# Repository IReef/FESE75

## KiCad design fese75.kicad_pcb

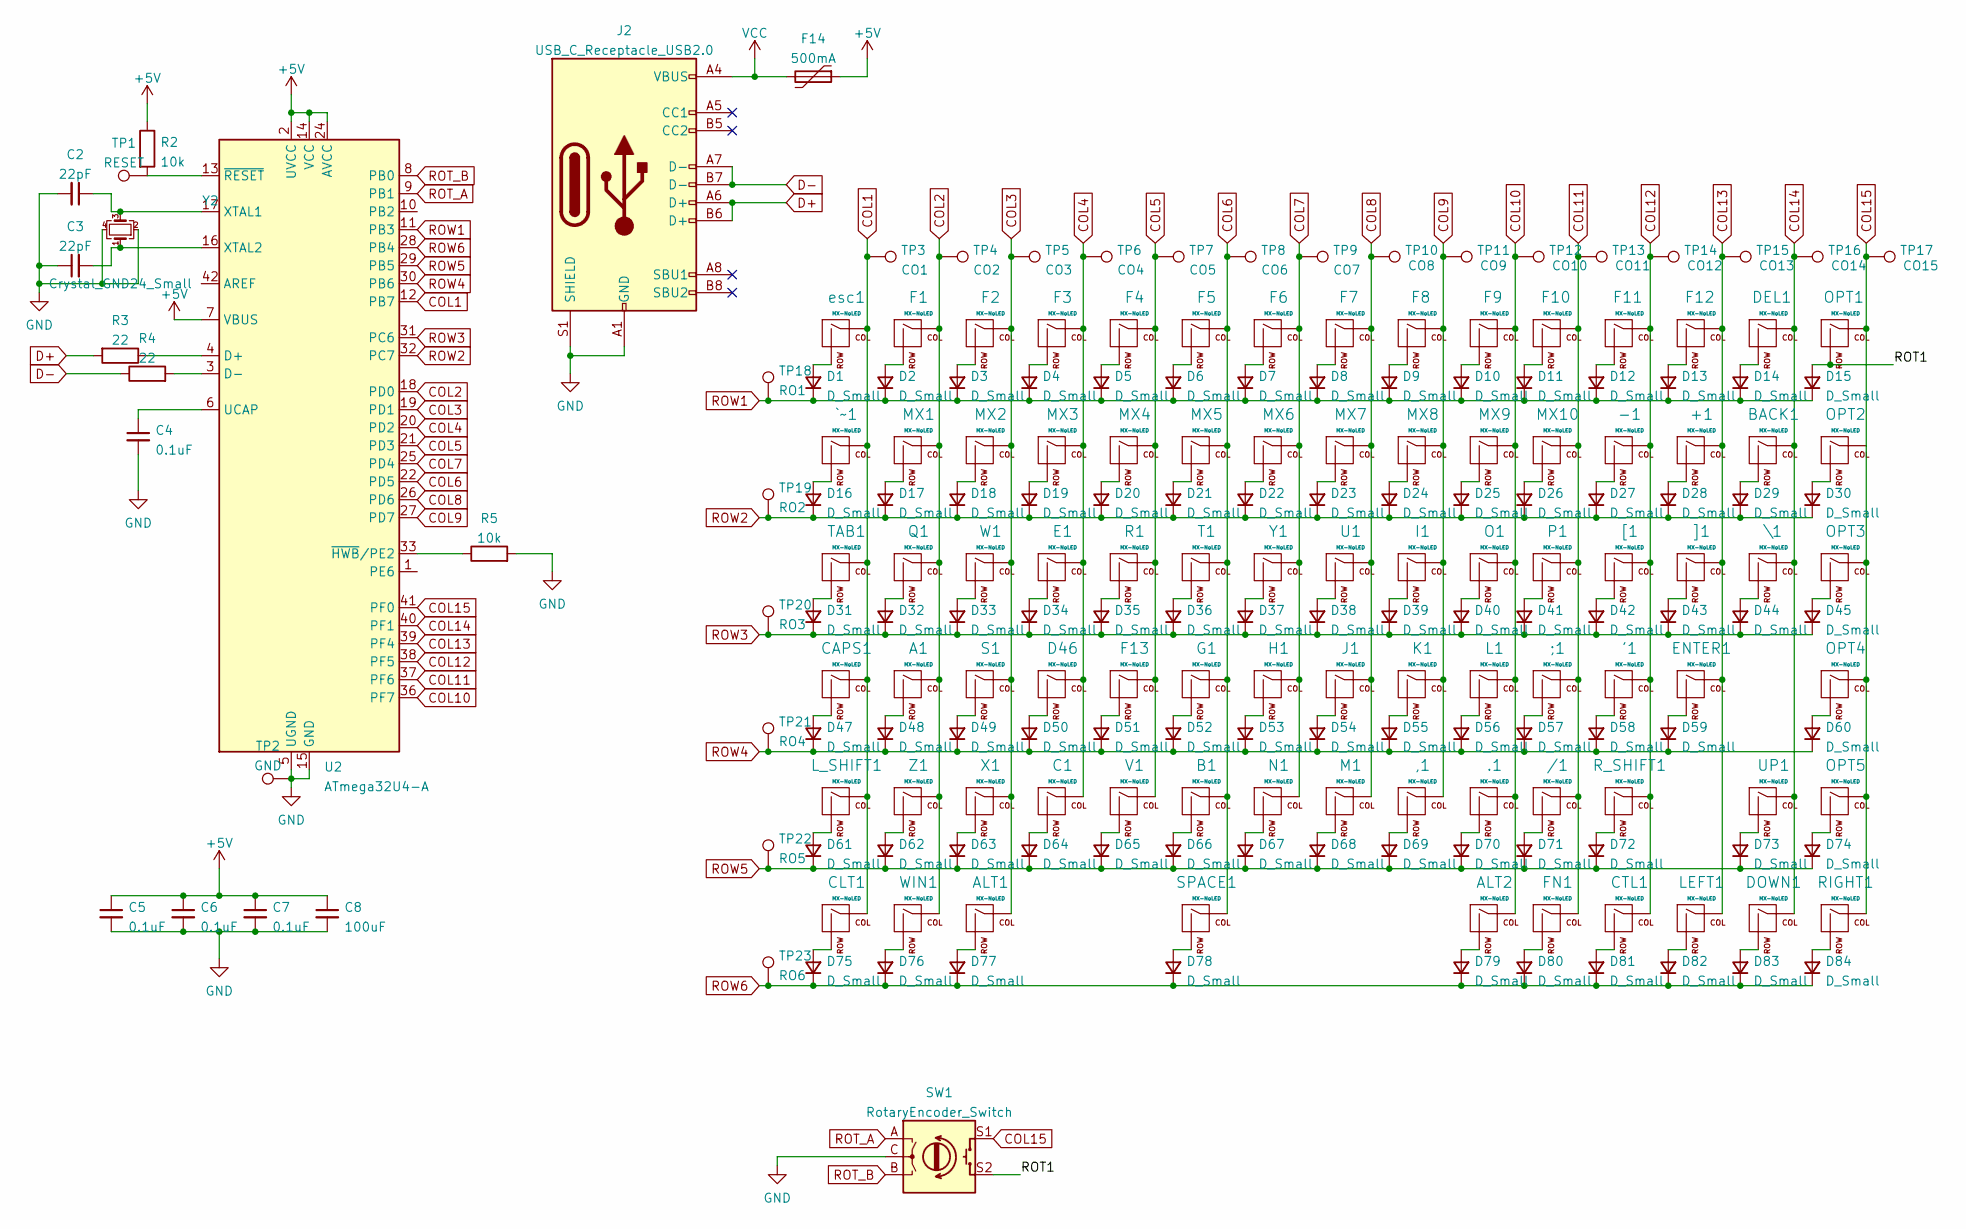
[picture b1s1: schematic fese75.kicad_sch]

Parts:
'1: MX-NoLED; SW_Hotswap_Kailh_1.00u
+1: MX-NoLED; SW_Hotswap_Kailh_1.00u
,1: MX-NoLED; SW_Hotswap_Kailh_1.00u
-1: MX-NoLED; SW_Hotswap_Kailh_1.00u
.1: MX-NoLED; SW_Hotswap_Kailh_1.00u
/1: MX-NoLED; SW_Hotswap_Kailh_1.00u
;1: MX-NoLED; SW_Hotswap_Kailh_1.00u
A1: MX-NoLED; SW_Hotswap_Kailh_1.00u
ALT1: MX-NoLED; SW_Hotswap_Kailh_1.25u
ALT2: MX-NoLED; SW_Hotswap_Kailh_1.00u
B1: MX-NoLED; SW_Hotswap_Kailh_1.00u
BACK1: MX-NoLED; SW_Hotswap_Kailh_2.00u
C1: MX-NoLED; SW_Hotswap_Kailh_1.00u
C2, C3: 22pF; C_0603_1608Metric
C4, C5, C6, C7: 0.1uF; C_0603_1608Metric
C8: 100uF; C_0603_1608Metric
CAPS1: MX-NoLED; SW_Hotswap_Kailh_1.75u
CLT1: MX-NoLED; SW_Hotswap_Kailh_1.25u
CTL1: MX-NoLED; SW_Hotswap_Kailh_1.00u
D1, D2, D3, D4, D5, D6, D7, D8, D9, D10, D11, D12, D13, D14, D15, D16, D17, D18, D19, D20, D21, D22, D23, D24, D25, D26, D27, D28, D29, D30, D31, D32, D33, D34, D35, D36, D37, D38, D39, D40, D41, D42, D43, D44, D45, D47, D48, D49, D50, D51, D52, D53, D54, D55, D56, D57, D58, D59, D60, D61, D62, D63, D64, D65, D66, D67, D68, D69, D70, D71, D72, D73, D74, D75, D76, D77, D78, D79, D80, D81, D82, D83, D84: D_Small; D_SOD-123
D46: MX-NoLED; SW_Hotswap_Kailh_1.00u
DEL1: MX-NoLED; SW_Hotswap_Kailh_1.00u
DOWN1: MX-NoLED; SW_Hotswap_Kailh_1.00u
E1: MX-NoLED; SW_Hotswap_Kailh_1.00u
ENTER1: MX-NoLED; SW_Hotswap_Kailh_2.25u
F1, F2, F3, F4, F5, F6, F7, F8, F9, F10, F11, F12, F13: MX-NoLED; SW_Hotswap_Kailh_1.00u
F14: 500mA; Fuse_1206_3216Metric
FN1: MX-NoLED; SW_Hotswap_Kailh_1.00u
G1: MX-NoLED; SW_Hotswap_Kailh_1.00u
H1: MX-NoLED; SW_Hotswap_Kailh_1.00u
I1: MX-NoLED; SW_Hotswap_Kailh_1.00u
J1: MX-NoLED; SW_Hotswap_Kailh_1.00u
J2: USB_C_Receptacle_USB2.0; USB_C_Receptacle_GCT_USB4085
K1: MX-NoLED; SW_Hotswap_Kailh_1.00u
L1: MX-NoLED; SW_Hotswap_Kailh_1.00u
LEFT1: MX-NoLED; SW_Hotswap_Kailh_1.00u
L_SHIFT1: MX-NoLED; SW_Hotswap_Kailh_2.25u
M1: MX-NoLED; SW_Hotswap_Kailh_1.00u
MX1, MX2, MX3, MX4, MX5, MX6, MX7, MX8, MX9, MX10: MX-NoLED; SW_Hotswap_Kailh_1.00u
N1: MX-NoLED; SW_Hotswap_Kailh_1.00u
O1: MX-NoLED; SW_Hotswap_Kailh_1.00u
OPT1, OPT2, OPT3, OPT4, OPT5: MX-NoLED; SW_Hotswap_Kailh_1.00u
P1: MX-NoLED; SW_Hotswap_Kailh_1.00u
Q1: MX-NoLED; SW_Hotswap_Kailh_1.00u
R1: MX-NoLED; SW_Hotswap_Kailh_1.00u
R2, R5: 10k; R_0603_1608Metric
R3, R4: 22; R_0603_1608Metric
RIGHT1: MX-NoLED; SW_Hotswap_Kailh_1.00u
R_SHIFT1: MX-NoLED; SW_Hotswap_Kailh_1.75u
S1: MX-NoLED; SW_Hotswap_Kailh_1.00u
SPACE1: MX-NoLED; SW_Hotswap_Kailh_6.25u
SW1: RotaryEncoder_Switch; RotaryEncoder_Alps_EC11E-Switch_Vertical_H20mm
T1: MX-NoLED; SW_Hotswap_Kailh_1.00u
TAB1: MX-NoLED; SW_Hotswap_Kailh_1.50u
TP1: RESET; TestPoint_THTPad_D1.0mm_Drill0.5mm
TP2: GND; TestPoint_THTPad_1.0x1.0mm_Drill0.5mm
TP3: CO1; TestPoint_THTPad_2.0x2.0mm_Drill1.0mm
TP4: CO2; TestPoint_THTPad_D2.0mm_Drill1.0mm
TP5: CO3; TestPoint_THTPad_D2.0mm_Drill1.0mm
TP6: CO4; TestPoint_THTPad_D2.0mm_Drill1.0mm
TP7: CO5; TestPoint_THTPad_D2.0mm_Drill1.0mm
TP8: CO6; TestPoint_THTPad_D2.0mm_Drill1.0mm
TP9: CO7; TestPoint_THTPad_D2.0mm_Drill1.0mm
TP10: CO8; TestPoint_THTPad_D2.0mm_Drill1.0mm
TP11: CO9; TestPoint_THTPad_D2.0mm_Drill1.0mm
TP12: CO10; TestPoint_THTPad_D2.0mm_Drill1.0mm
TP13: CO11; TestPoint_THTPad_D2.0mm_Drill1.0mm
TP14: CO12; TestPoint_THTPad_D2.0mm_Drill1.0mm
TP15: CO13; TestPoint_THTPad_D2.0mm_Drill1.0mm
TP16: CO14; TestPoint_THTPad_D2.0mm_Drill1.0mm
TP17: CO15; TestPoint_THTPad_D2.0mm_Drill1.0mm
TP18: RO1; TestPoint_THTPad_2.0x2.0mm_Drill1.0mm
TP19: RO2; TestPoint_THTPad_D2.0mm_Drill1.0mm
TP20: RO3; TestPoint_THTPad_D2.0mm_Drill1.0mm
TP21: RO4; TestPoint_THTPad_D2.0mm_Drill1.0mm
TP22: RO5; TestPoint_THTPad_D2.0mm_Drill1.0mm
TP23: RO6; TestPoint_THTPad_D2.0mm_Drill1.0mm
U1: MX-NoLED; SW_Hotswap_Kailh_1.00u
U2: ATmega32U4-A; TQFP-44_10x10mm_P0.8mm
UP1: MX-NoLED; SW_Hotswap_Kailh_1.00u
V1: MX-NoLED; SW_Hotswap_Kailh_1.00u
W1: MX-NoLED; SW_Hotswap_Kailh_1.00u
WIN1: MX-NoLED; SW_Hotswap_Kailh_1.25u
X1: MX-NoLED; SW_Hotswap_Kailh_1.00u
Y1: MX-NoLED; SW_Hotswap_Kailh_1.00u
Y2: Crystal_GND24_Small; Crystal_SMD_3225-4Pin_3.2x2.5mm
Z1: MX-NoLED; SW_Hotswap_Kailh_1.00u
[1: MX-NoLED; SW_Hotswap_Kailh_1.00u
\1: MX-NoLED; SW_Hotswap_Kailh_1.50u
]1: MX-NoLED; SW_Hotswap_Kailh_1.00u
`~1: MX-NoLED; SW_Hotswap_Kailh_1.00u
esc1: MX-NoLED; SW_Hotswap_Kailh_1.00u

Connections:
+5V: C5.1, C6.1, C7.1, C8.1, F14.1, R2.1, U2.2 (UVCC), U2.7 (VBUS), U2.14 (VCC), U2.24 (AVCC), U2.34 (VCC), U2.44 (AVCC)
/ROT1: D15.2 (A), OPT1.2 (ROW), SW1.S2
COL1: CAPS1.1 (COL), CLT1.1 (COL), L_SHIFT1.1 (COL), TAB1.1 (COL), TP3.1, U2.12 (PB7), `~1.1 (COL), esc1.1 (COL)
COL2: A1.1 (COL), F1.1 (COL), MX1.1 (COL), Q1.1 (COL), TP4.1, U2.18 (PD0), WIN1.1 (COL), Z1.1 (COL)
COL3: ALT1.1 (COL), F2.1 (COL), MX2.1 (COL), S1.1 (COL), TP5.1, U2.19 (PD1), W1.1 (COL), X1.1 (COL)
COL4: C1.1 (COL), D46.1 (COL), E1.1 (COL), F3.1 (COL), MX3.1 (COL), TP6.1, U2.20 (PD2)
COL5: F4.1 (COL), F13.1 (COL), MX4.1 (COL), R1.1 (COL), TP7.1, U2.21 (PD3), V1.1 (COL)
COL6: B1.1 (COL), F5.1 (COL), G1.1 (COL), MX5.1 (COL), SPACE1.1 (COL), T1.1 (COL), TP8.1, U2.22 (PD5)
COL7: F6.1 (COL), H1.1 (COL), MX6.1 (COL), N1.1 (COL), TP9.1, U2.25 (PD4), Y1.1 (COL)
COL8: F7.1 (COL), J1.1 (COL), M1.1 (COL), MX7.1 (COL), TP10.1, U1.1 (COL), U2.26 (PD6)
COL9: ,1.1 (COL), F8.1 (COL), I1.1 (COL), K1.1 (COL), MX8.1 (COL), TP11.1, U2.27 (PD7)
COL10: .1.1 (COL), ALT2.1 (COL), F9.1 (COL), L1.1 (COL), MX9.1 (COL), O1.1 (COL), TP12.1, U2.36 (PF7)
COL11: /1.1 (COL), ;1.1 (COL), F10.1 (COL), FN1.1 (COL), MX10.1 (COL), P1.1 (COL), TP13.1, U2.37 (PF6)
COL12: '1.1 (COL), -1.1 (COL), CTL1.1 (COL), F11.1 (COL), R_SHIFT1.1 (COL), TP14.1, U2.38 (PF5), [1.1 (COL)
COL13: +1.1 (COL), ENTER1.1 (COL), F12.1 (COL), LEFT1.1 (COL), TP15.1, U2.39 (PF4), ]1.1 (COL)
COL14: BACK1.1 (COL), DEL1.1 (COL), DOWN1.1 (COL), TP16.1, U2.40 (PF1), UP1.1 (COL), \1.1 (COL)
COL15: OPT1.1 (COL), OPT2.1 (COL), OPT3.1 (COL), OPT4.1 (COL), OPT5.1 (COL), RIGHT1.1 (COL), SW1.S1, TP17.1, U2.41 (PF0)
D+: J2.A6 (D+), J2.B6 (D+), R3.2
D-: J2.A7 (D-), J2.B7 (D-), R4.1
GND: C2.2, C3.1, C4.2, C5.2, C6.2, C7.2, C8.2, J2.A1 (GND), J2.A12 (GND), J2.B1 (GND), J2.B12 (GND), J2.S1 (SHIELD), R5.2, SW1.C, TP2.1, U2.5 (UGND), U2.15 (GND), U2.23 (GND), U2.35 (GND), U2.43 (GND), Y2.2, Y2.4
unnamed: '1.2 (ROW), D58.2 (A)
unnamed: +1.2 (ROW), D28.2 (A)
unnamed: ,1.2 (ROW), D69.2 (A)
unnamed: -1.2 (ROW), D27.2 (A)
unnamed: .1.2 (ROW), D70.2 (A)
unnamed: /1.2 (ROW), D71.2 (A)
unnamed: ;1.2 (ROW), D57.2 (A)
unnamed: A1.2 (ROW), D48.2 (A)
unnamed: ALT1.2 (ROW), D77.2 (A)
unnamed: ALT2.2 (ROW), D79.2 (A)
unnamed: B1.2 (ROW), D66.2 (A)
unnamed: BACK1.2 (ROW), D29.2 (A)
unnamed: C1.2 (ROW), D64.2 (A)
unnamed: C2.1, U2.17 (XTAL1), Y2.3
unnamed: C3.2, U2.16 (XTAL2), Y2.1
unnamed: C4.1, U2.6 (UCAP)
unnamed: CAPS1.2 (ROW), D47.2 (A)
unnamed: CLT1.2 (ROW), D75.2 (A)
unnamed: CTL1.2 (ROW), D81.2 (A)
unnamed: D1.2 (A), esc1.2 (ROW)
unnamed: D2.2 (A), F1.2 (ROW)
unnamed: D3.2 (A), F2.2 (ROW)
unnamed: D4.2 (A), F3.2 (ROW)
unnamed: D5.2 (A), F4.2 (ROW)
unnamed: D6.2 (A), F5.2 (ROW)
unnamed: D7.2 (A), F6.2 (ROW)
unnamed: D8.2 (A), F7.2 (ROW)
unnamed: D9.2 (A), F8.2 (ROW)
unnamed: D10.2 (A), F9.2 (ROW)
unnamed: D11.2 (A), F10.2 (ROW)
unnamed: D12.2 (A), F11.2 (ROW)
unnamed: D13.2 (A), F12.2 (ROW)
unnamed: D14.2 (A), DEL1.2 (ROW)
unnamed: D16.2 (A), `~1.2 (ROW)
unnamed: D17.2 (A), MX1.2 (ROW)
unnamed: D18.2 (A), MX2.2 (ROW)
unnamed: D19.2 (A), MX3.2 (ROW)
unnamed: D20.2 (A), MX4.2 (ROW)
unnamed: D21.2 (A), MX5.2 (ROW)
unnamed: D22.2 (A), MX6.2 (ROW)
unnamed: D23.2 (A), MX7.2 (ROW)
unnamed: D24.2 (A), MX8.2 (ROW)
unnamed: D25.2 (A), MX9.2 (ROW)
unnamed: D26.2 (A), MX10.2 (ROW)
unnamed: D30.2 (A), OPT2.2 (ROW)
unnamed: D31.2 (A), TAB1.2 (ROW)
unnamed: D32.2 (A), Q1.2 (ROW)
unnamed: D33.2 (A), W1.2 (ROW)
unnamed: D34.2 (A), E1.2 (ROW)
unnamed: D35.2 (A), R1.2 (ROW)
unnamed: D36.2 (A), T1.2 (ROW)
unnamed: D37.2 (A), Y1.2 (ROW)
unnamed: D38.2 (A), U1.2 (ROW)
unnamed: D39.2 (A), I1.2 (ROW)
unnamed: D40.2 (A), O1.2 (ROW)
unnamed: D41.2 (A), P1.2 (ROW)
unnamed: D42.2 (A), [1.2 (ROW)
unnamed: D43.2 (A), ]1.2 (ROW)
unnamed: D44.2 (A), \1.2 (ROW)
unnamed: D45.2 (A), OPT3.2 (ROW)
unnamed: D46.2 (ROW), D50.2 (A)
unnamed: D49.2 (A), S1.2 (ROW)
unnamed: D51.2 (A), F13.2 (ROW)
unnamed: D52.2 (A), G1.2 (ROW)
unnamed: D53.2 (A), H1.2 (ROW)
unnamed: D54.2 (A), J1.2 (ROW)
unnamed: D55.2 (A), K1.2 (ROW)
unnamed: D56.2 (A), L1.2 (ROW)
unnamed: D59.2 (A), ENTER1.2 (ROW)
unnamed: D60.2 (A), OPT4.2 (ROW)
unnamed: D61.2 (A), L_SHIFT1.2 (ROW)
unnamed: D62.2 (A), Z1.2 (ROW)
unnamed: D63.2 (A), X1.2 (ROW)
unnamed: D65.2 (A), V1.2 (ROW)
unnamed: D67.2 (A), N1.2 (ROW)
unnamed: D68.2 (A), M1.2 (ROW)
unnamed: D72.2 (A), R_SHIFT1.2 (ROW)
unnamed: D73.2 (A), UP1.2 (ROW)
unnamed: D74.2 (A), OPT5.2 (ROW)
unnamed: D76.2 (A), WIN1.2 (ROW)
unnamed: D78.2 (A), SPACE1.2 (ROW)
unnamed: D80.2 (A), FN1.2 (ROW)
unnamed: D82.2 (A), LEFT1.2 (ROW)
unnamed: D83.2 (A), DOWN1.2 (ROW)
unnamed: D84.2 (A), RIGHT1.2 (ROW)
unnamed: R2.2, TP1.1, U2.13 (~RESET)
unnamed: R3.1, U2.4 (D+)
unnamed: R4.2, U2.3 (D-)
unnamed: R5.1, U2.33 (~HWB/PE2)
ROT_A: SW1.A, U2.9 (PB1)
ROT_B: SW1.B, U2.8 (PB0)
ROW1: D1.1 (K), D2.1 (K), D3.1 (K), D4.1 (K), D5.1 (K), D6.1 (K), D7.1 (K), D8.1 (K), D9.1 (K), D10.1 (K), D11.1 (K), D12.1 (K), D13.1 (K), D14.1 (K), D15.1 (K), TP18.1, U2.11 (PB3)
ROW2: D16.1 (K), D17.1 (K), D18.1 (K), D19.1 (K), D20.1 (K), D21.1 (K), D22.1 (K), D23.1 (K), D24.1 (K), D25.1 (K), D26.1 (K), D27.1 (K), D28.1 (K), D29.1 (K), D30.1 (K), TP19.1, U2.32 (PC7)
ROW3: D31.1 (K), D32.1 (K), D33.1 (K), D34.1 (K), D35.1 (K), D36.1 (K), D37.1 (K), D38.1 (K), D39.1 (K), D40.1 (K), D41.1 (K), D42.1 (K), D43.1 (K), D44.1 (K), D45.1 (K), TP20.1, U2.31 (PC6)
ROW4: D47.1 (K), D48.1 (K), D49.1 (K), D50.1 (K), D51.1 (K), D52.1 (K), D53.1 (K), D54.1 (K), D55.1 (K), D56.1 (K), D57.1 (K), D58.1 (K), D59.1 (K), D60.1 (K), TP21.1, U2.30 (PB6)
ROW5: D61.1 (K), D62.1 (K), D63.1 (K), D64.1 (K), D65.1 (K), D66.1 (K), D67.1 (K), D68.1 (K), D69.1 (K), D70.1 (K), D71.1 (K), D72.1 (K), D73.1 (K), D74.1 (K), TP22.1, U2.29 (PB5)
ROW6: D75.1 (K), D76.1 (K), D77.1 (K), D78.1 (K), D79.1 (K), D80.1 (K), D81.1 (K), D82.1 (K), D83.1 (K), D84.1 (K), TP23.1, U2.28 (PB4)
VCC: F14.2, J2.A4 (VBUS), J2.A9 (VBUS), J2.B4 (VBUS), J2.B9 (VBUS)

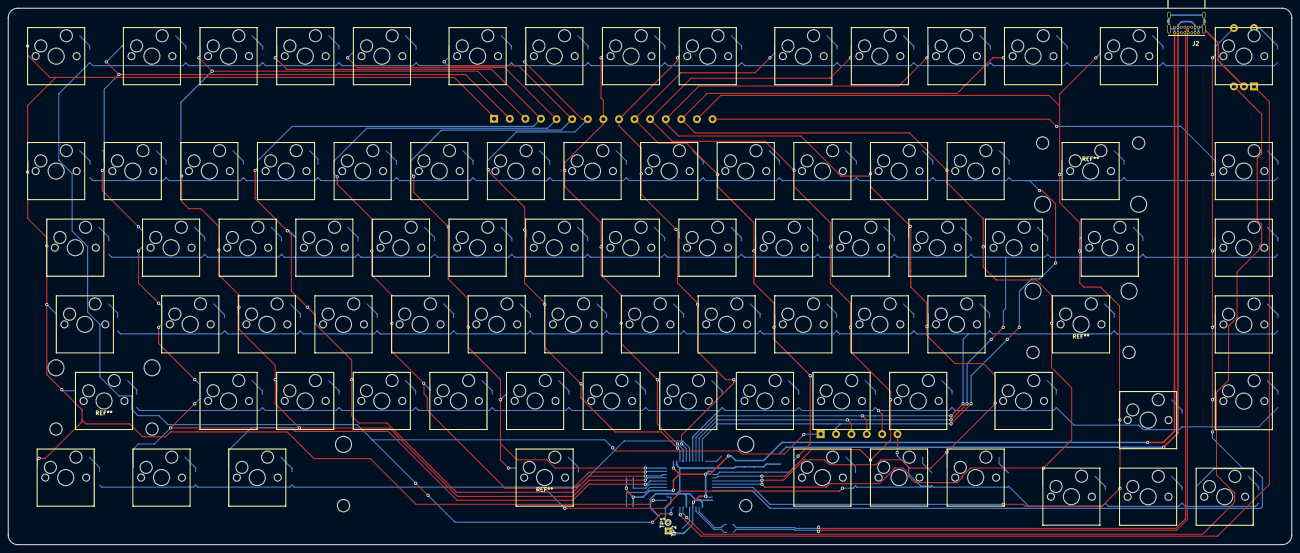
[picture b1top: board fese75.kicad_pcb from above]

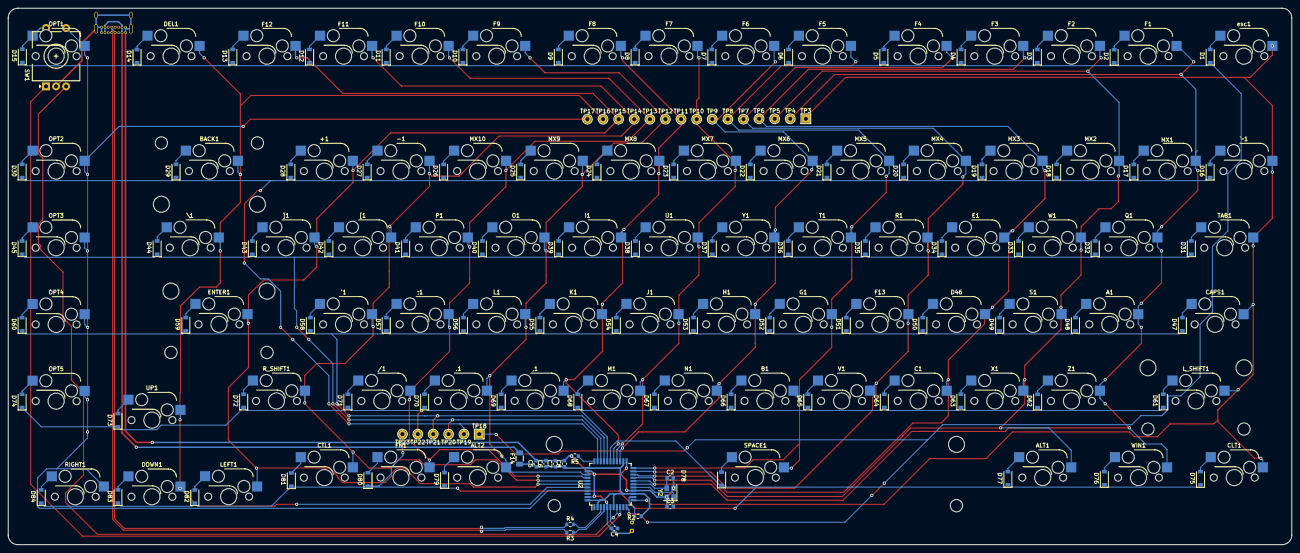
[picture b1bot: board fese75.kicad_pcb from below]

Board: 2 copper layers, 319.1 x 133.3 mm, 205 parts (119 on the bottom side), 118 nets.

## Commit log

2022-01-03 Project initial
2022-01-06 Keyboard matrix sch
2022-01-06 quick place component
2022-01-11 align layout
2022-01-11 add stabilizer hole
2022-01-12 routing pcb
2022-01-12 fix some missing footprint
2022-01-12 add type c and expand power
2022-01-12 fix2
2022-01-12 add testpoint
2022-01-12 Finalize1
2022-01-12 connect missing trace
2022-01-12 add graphic
2022-01-13 fix missing stab bug
2022-01-14 fix missing trace
2022-02-13 change distant from 0.5 to 0.25
